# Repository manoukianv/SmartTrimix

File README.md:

# SmartTrimix
Trimix Analyzer /!\ do not used for dive or plan !!!

# It's a experimental and training project, do NOT USE TO PLAN A DIVE !
Always use a professional analyzer.

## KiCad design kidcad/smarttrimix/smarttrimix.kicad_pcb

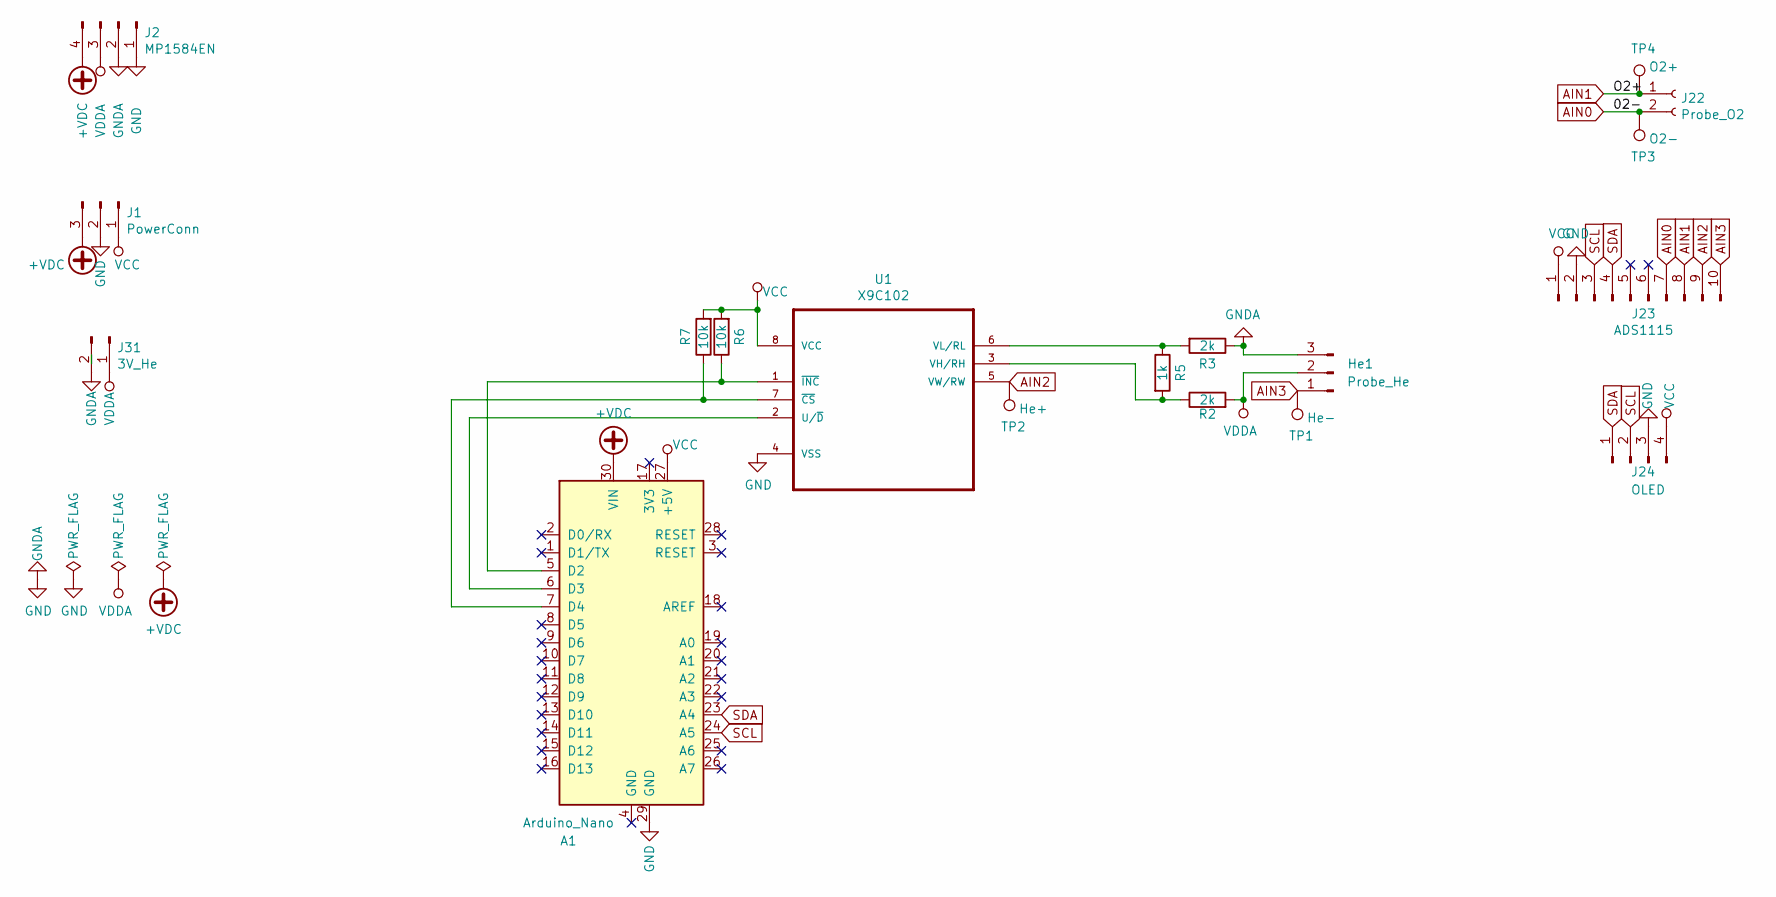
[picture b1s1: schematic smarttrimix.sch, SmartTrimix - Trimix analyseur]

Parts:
A1: Arduino_Nano
He1: Probe_He; JST_EH_B03B-EH-A_1x03_P2.50mm_Vertical
J1: PowerConn; JST_EH_B03B-EH-A_1x03_P2.50mm_Vertical
J2: MP1584EN
J22: Probe_O2; JST_EH_B02B-EH-A_1x02_P2.50mm_Vertical
J23: ADS1115; PinSocket_1x10_P2.54mm_Vertical
J24: OLED; JST_EH_B04B-EH-A_1x04_P2.50mm_Vertical
J31: 3V_He; JST_EH_B02B-EH-A_1x02_P2.50mm_Vertical
R2, R3: 2k; R_Axial_DIN0207_L6.3mm_D2.5mm_P10.16mm_Horizontal
R5: 1k; R_Axial_DIN0207_L6.3mm_D2.5mm_P10.16mm_Horizontal
R6, R7: 10k; R_Axial_DIN0207_L6.3mm_D2.5mm_P10.16mm_Horizontal
TP1: He-; TestPoint_THTPad_D1.0mm_Drill0.5mm
TP2: He+; TestPoint_THTPad_D1.0mm_Drill0.5mm
TP3: O2-; TestPoint_THTPad_D1.0mm_Drill0.5mm
TP4: O2+; TestPoint_THTPad_D1.0mm_Drill0.5mm
U1: X9C102; DIP254P762X533-8

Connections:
+VDC: A1.30 (VIN), J1.3, J2.4
AIN0: J22.2, J23.7, TP3.1
AIN1: J22.1, J23.8, TP4.1
AIN2: J23.9, TP2.1, U1.5 (VW/RW)
AIN3: He1.1, J23.10, TP1.1
GND: A1.29 (GND), He1.3, J1.2, J2.1, J2.2, J23.2, J24.3, J31.2, R3.1, U1.4 (VSS)
unnamed: A1.5 (D2), R6.1, U1.1 (~INC)
unnamed: A1.6 (D3), U1.2 (U/~D)
unnamed: A1.7 (D4), R7.1, U1.7 (~CS)
unnamed: R2.1, R5.2, U1.3 (VH/RH)
unnamed: R3.2, R5.1, U1.6 (VL/RL)
SCL: A1.24 (A5), J23.3, J24.2
SDA: A1.23 (A4), J23.4, J24.1
VCC: A1.27 (+5V), J1.1, J23.1, J24.4, R6.2, R7.2, U1.8 (VCC)
VDDA: He1.2, J2.3, J31.1, R2.2

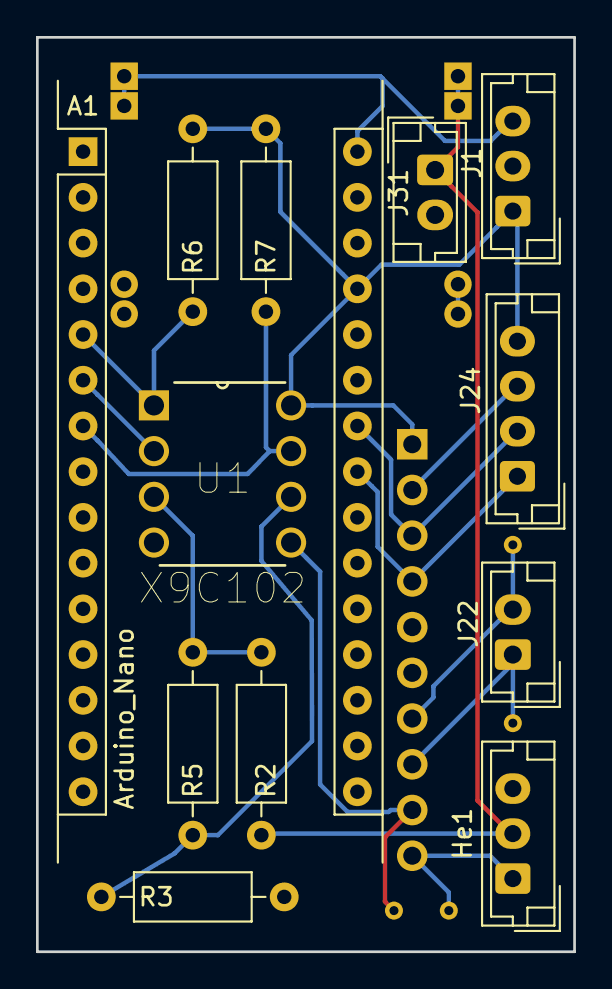
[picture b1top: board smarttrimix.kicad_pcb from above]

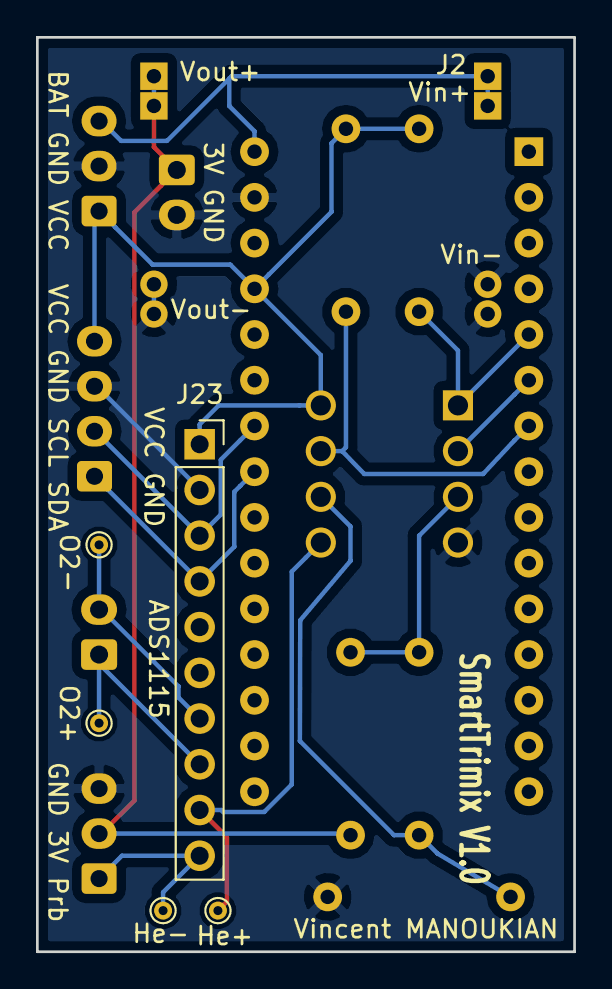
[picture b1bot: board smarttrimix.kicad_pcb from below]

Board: 2 copper layers, 29.8 x 50.8 mm, 18 parts (6 on the bottom side), 15 nets.

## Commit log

2020-04-17 Init repo
2020-04-17 Add platformio.ini file
